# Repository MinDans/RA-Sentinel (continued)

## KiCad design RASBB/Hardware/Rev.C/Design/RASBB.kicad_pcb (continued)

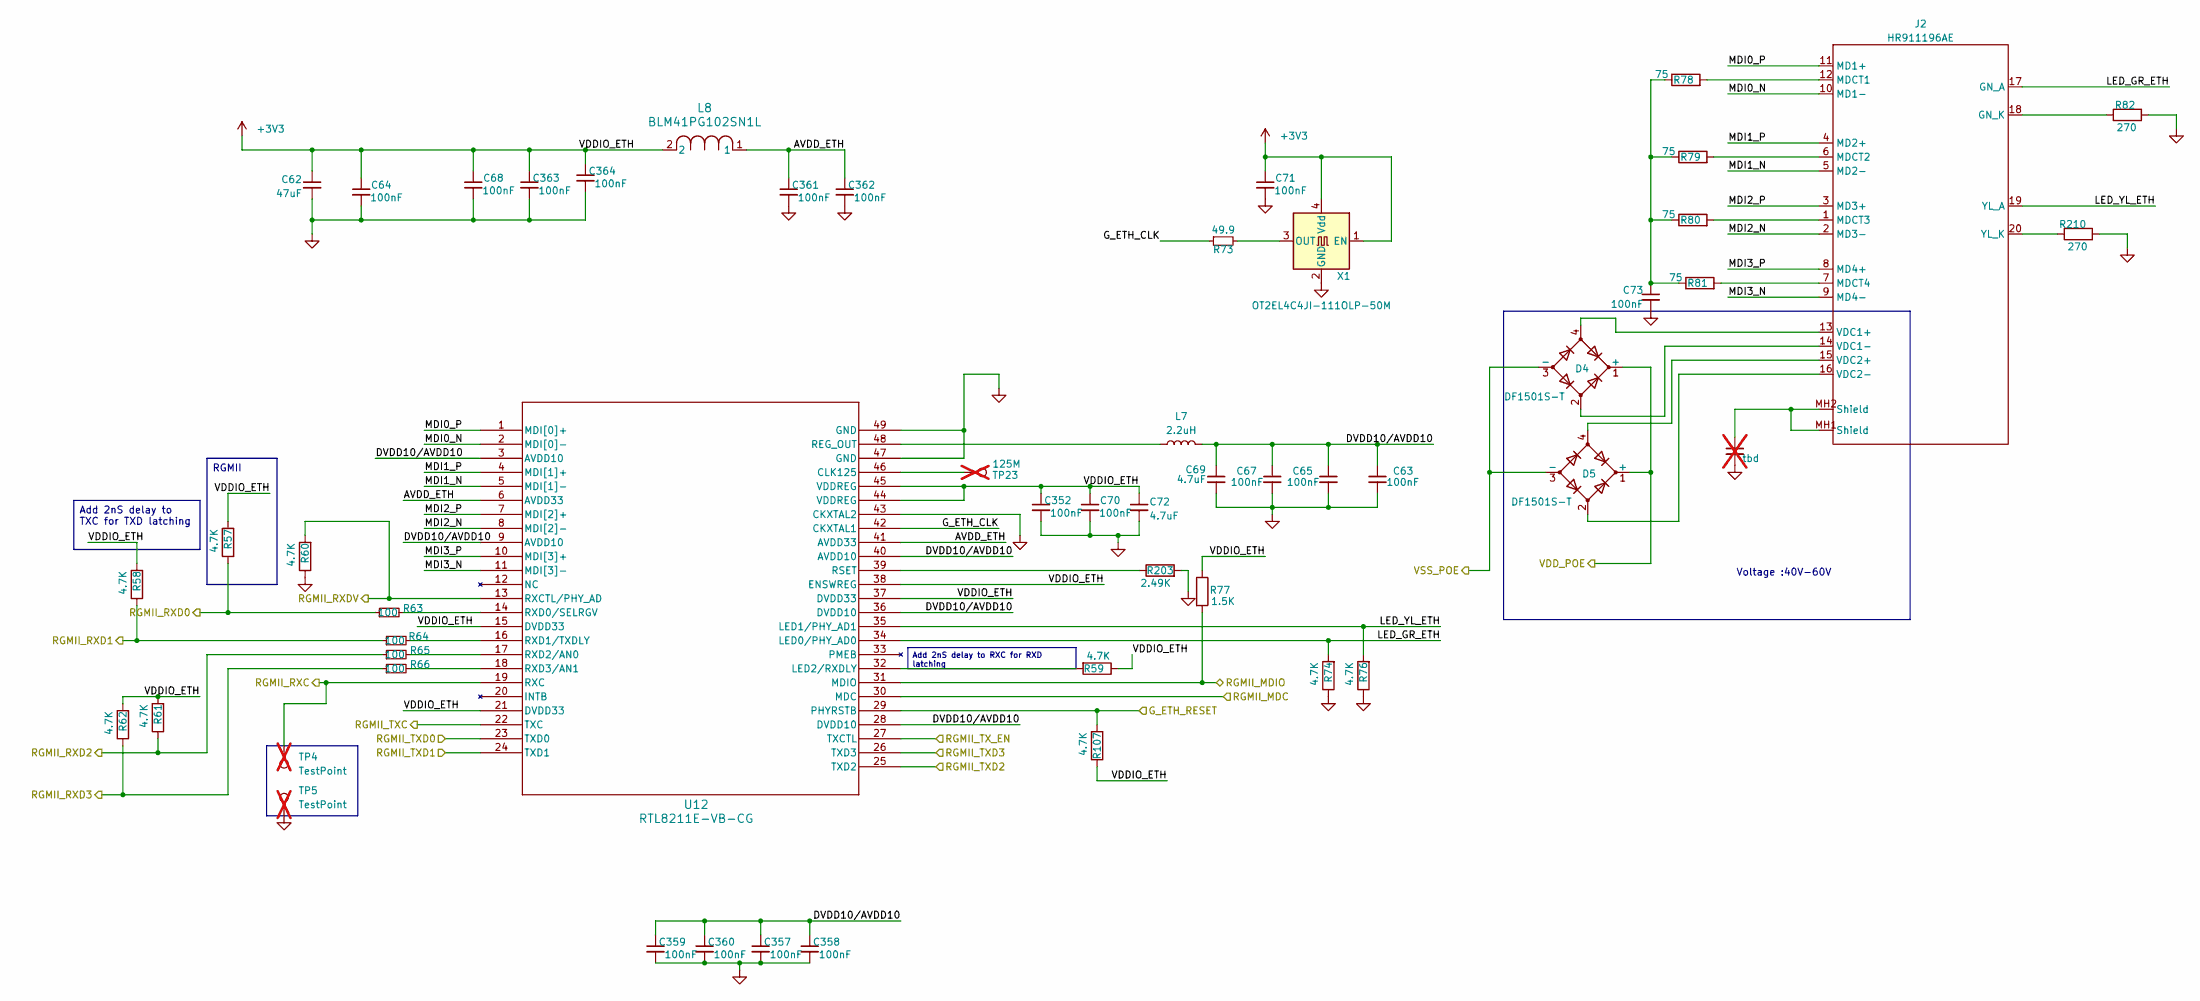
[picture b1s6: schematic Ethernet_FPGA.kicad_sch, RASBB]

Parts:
C62: 47uF; C_0805_2012Metric; Mfr. Part # GRM21BR61A476ME15L; LCSC Part # C124129
C63, C64, C65, C67, C68, C70, C71, C352, C357, C358, C359, C360, C361, C362, C363, C364: 100nF; C_0402_1005Metric; Mfr. Part # 0402B104K500CT; LCSC Part # C152814
C69, C72: 4.7uF; C_0402_1005Metric; Mfr. Part # GRM155R61A475KEAAD; LCSC Part # C77004
C73: 100nF; C_2220_5750Metric; Mfr. Part # FV55X104K202EGG; LCSC Part # C5290327
C74: tbd; C_1206_3216Metric; not fitted
D4, D5: DF1501S-T; DF1501ST; Mfr. Part # DF1501S-T; LCSC Part # C155338
J2: HR911196AE; JK00229NL; Mfr. Part # HR911196AE; LCSC Part # C5149194
L7: 2.2uH; L_1206_3216Metric; Mfr. Part # MGFL3216F2R2MT-LF; LCSC Part # C486337
L8: BLM41PG102SN1L; IND_BLM41_1806_MUR-M; Mfr. Part # BLM41PG102SN1L; LCSC Part # C88999
R57, R58, R59, R60, R61, R62, R74, R76, R107: 4.7K; R_0402_1005Metric; Mfr. Part # WR04X4701FTL; LCSC Part # C163826
R63, R64, R65, R66: 100; R_0402_1005Metric; Mfr. Part # WR04X1000FTL; LCSC Part # C163808
R73: 49.9; R_0402_1005Metric; Mfr. Part # RMCF0402FT49R9; LCSC Part # C4229190
R77: 1.5K; R_0402_1005Metric; Mfr. Part # WR04X152JTL; LCSC Part # C384376
R78, R79, R80, R81: 75; R_0603_1608Metric; Mfr. Part # ESR03EZPF75R0; LCSC Part # C2074227
R82, R210: 270; R_0402_1005Metric; Mfr. Part # SR04X271JTL; LCSC Part # C880838
R203: 2.49K; R_0402_1005Metric; Mfr. Part # RC0402FR-072K49L; LCSC Part # C114768
TP4, TP5: TestPoint; TestPoint_Pad_D1.0mm; not fitted
TP23: 125M; TestPoint_Pad_D1.0mm; not fitted
U12: RTL8211E-VB-CG; QFN48_6X6X0P85_RTK; Mfr. Part # RTL8211E-VB-CG; LCSC Part # C90735
X1: OT2EL4C4JI-111OLP-50M; Oscillator_SMD_Abracon_ASE-4Pin_3.2x2.5mm; Mfr. Part # OT2EL4C4JI-111OLP-50M; LCSC Part # C5203552

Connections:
+3V3: C62.1, C64.1, C68.1, C70.1, C71.1, C72.1, C352.1, C363.1, C364.1, L8.2, R57.2, R58.2, R59.1, R61.2, R62.2, R77.1, R107.1, U12.15 (DVDD33), U12.21 (DVDD33), U12.37 (DVDD33), U12.38 (ENSWREG), U12.44 (VDDREG), U12.45 (VDDREG), X1.1 (EN), X1.4 (Vdd); also elsewhere on the board
/Ethernet_FPGA/AVDD_ETH: C361.1, C362.1, L8.1, U12.6 (AVDD33), U12.41 (AVDD33)
/Ethernet_FPGA/DVDD10/AVDD10: C63.1, C65.1, C67.1, C69.1, C357.1, C358.1, C359.1, C360.1, L7.1, U12.3 (AVDD10), U12.9 (AVDD10), U12.28 (DVDD10), U12.36 (DVDD10), U12.40 (AVDD10)
/Ethernet_FPGA/G_ETH_CLK: R73.1, U12.42 (CKXTAL1)
/Ethernet_FPGA/G_ETH_RESET: R107.2, U12.29 (PHYRSTB); also elsewhere on the board
/Ethernet_FPGA/LED_GR_ETH: J2.17 (GN_A), R74.2, U12.34 (LED0/PHY_AD0)
/Ethernet_FPGA/LED_YL_ETH: J2.19 (YL_A), R76.2, U12.35 (LED1/PHY_AD1)
/Ethernet_FPGA/MDI0_N: J2.10 (MD1-), U12.2 (MDI[0]-)
/Ethernet_FPGA/MDI0_P: J2.11 (MD1+), U12.1 (MDI[0]+)
/Ethernet_FPGA/MDI1_N: J2.5 (MD2-), U12.5 (MDI[1]-)
/Ethernet_FPGA/MDI1_P: J2.4 (MD2+), U12.4 (MDI[1]+)
/Ethernet_FPGA/MDI2_N: J2.2 (MD3-), U12.8 (MDI[2]-)
/Ethernet_FPGA/MDI2_P: J2.3 (MD3+), U12.7 (MDI[2]+)
/Ethernet_FPGA/MDI3_N: J2.9 (MD4-), U12.11 (MDI[3]-)
/Ethernet_FPGA/MDI3_P: J2.8 (MD4+), U12.10 (MDI[3]+)
/Ethernet_FPGA/RGMII_MDC: U12.30 (MDC); also elsewhere on the board
/Ethernet_FPGA/RGMII_MDIO: R77.2, U12.31 (MDIO); also elsewhere on the board
/Ethernet_FPGA/RGMII_RXC: TP4.1 (1_1), U12.19 (RXC); also elsewhere on the board
/Ethernet_FPGA/RGMII_RXD0: R57.1, R63.1; also elsewhere on the board
/Ethernet_FPGA/RGMII_RXD1: R58.1, R64.1; also elsewhere on the board
/Ethernet_FPGA/RGMII_RXD2: R61.1, R65.1; also elsewhere on the board
/Ethernet_FPGA/RGMII_RXD3: R62.1, R66.1; also elsewhere on the board
/Ethernet_FPGA/RGMII_RXDV: R60.2, U12.13 (RXCTL/PHY_AD); also elsewhere on the board
/Ethernet_FPGA/RGMII_TXC: U12.22 (TXC); also elsewhere on the board
/Ethernet_FPGA/RGMII_TXD0: U12.23 (TXD0); also elsewhere on the board
/Ethernet_FPGA/RGMII_TXD1: U12.24 (TXD1); also elsewhere on the board
/Ethernet_FPGA/RGMII_TXD2: U12.25 (TXD2); also elsewhere on the board
/Ethernet_FPGA/RGMII_TXD3: U12.26 (TXD3); also elsewhere on the board
/Ethernet_FPGA/RGMII_TX_EN: U12.27 (TXCTL); also elsewhere on the board
/VDC_IN: D4.1 (+), D5.1 (+); also elsewhere on the board
/VSS_POE: D4.3 (-), D5.3 (-); also elsewhere on the board
GND: C62.2, C63.2, C64.2, C65.2, C67.2, C68.2, C69.2, C70.2, C71.2, C72.2, C73.2, C74.2, C352.2, C357.2, C358.2, C359.2, C360.2, C361.2, C362.2, C363.2, C364.2, R60.1, R74.1, R76.1, R82.2, R203.2, R210.2, TP5.1 (1_1), U12.43 (CKXTAL2), U12.47 (GND), U12.49 (GND), X1.2 (GND); also elsewhere on the board
unnamed: C73.1, R78.1, R79.1, R80.1, R81.1
unnamed: C74.1, J2.MH1 (Shield), J2.MH2 (Shield)
unnamed: J2.18 (GN_K), R82.1
unnamed: J2.12 (MDCT1), R78.2
unnamed: J2.6 (MDCT2), R79.2
unnamed: J2.1 (MDCT3), R80.2
unnamed: J2.7 (MDCT4), R81.2
unnamed: D4.4, J2.13 (VDC1+)
unnamed: D4.2, J2.14 (VDC1-)
unnamed: D5.4, J2.15 (VDC2+)
unnamed: D5.2, J2.16 (VDC2-)
unnamed: J2.20 (YL_K), R210.1
unnamed: TP23.1 (1_1), U12.46 (CLK125)
unnamed: R59.2, U12.32 (LED2/RXDLY)
unnamed: L7.2, U12.48 (REG_OUT)
unnamed: R203.1, U12.39 (RSET)
unnamed: R63.2, U12.14 (RXD0/SELRGV)
unnamed: R64.2, U12.16 (RXD1/TXDLY)
unnamed: R65.2, U12.17 (RXD2/AN0)
unnamed: R66.2, U12.18 (RXD3/AN1)
unnamed: R73.2, X1.3 (OUT)

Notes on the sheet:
Voltage :40V-60V
Add 2nS delay to TXC for TXD latching
RGMII
Add 2nS delay to RXC for RXD latching

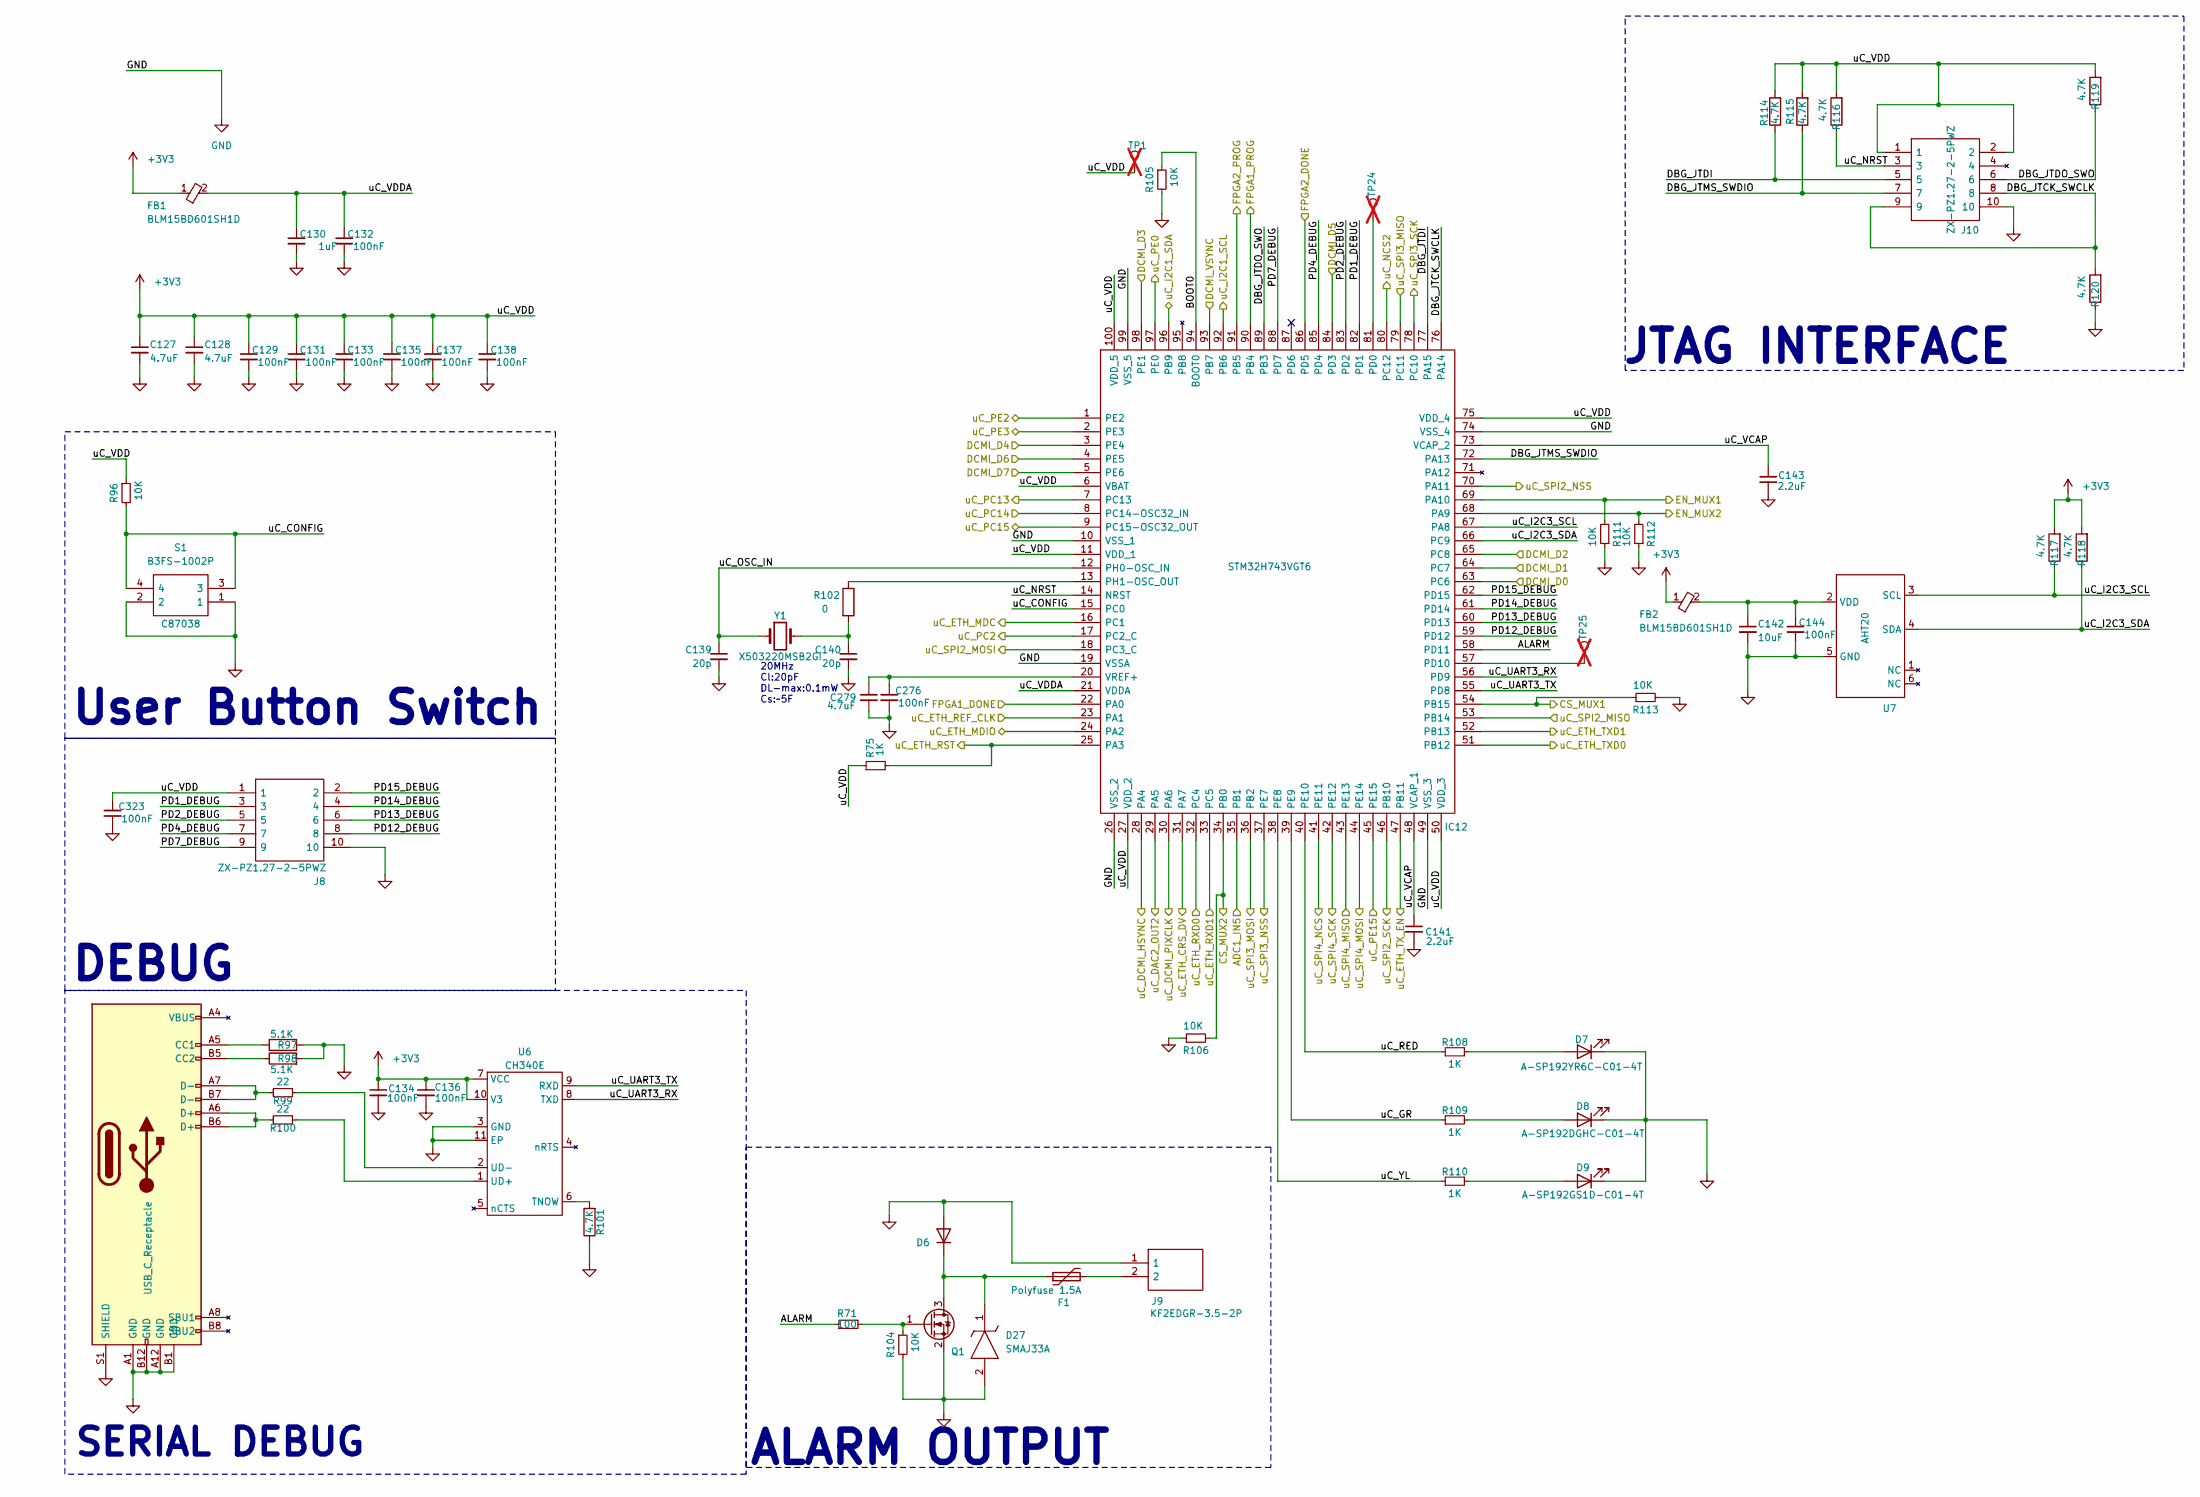
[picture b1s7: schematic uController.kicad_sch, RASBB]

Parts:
C127, C128, C279: 4.7uF; C_0603_1608Metric; Mfr. Part # GMK107BBJ475KA-T; LCSC Part # C7281848
C129, C131, C132, C133, C134, C135, C136, C137, C138, C144, C276, C323: 100nF; C_0402_1005Metric; Mfr. Part # 0402B104K500CT; LCSC Part # C152814
C130: 1uF; C_0402_1005Metric; Mfr. Part # 0402X105M160CT; LCSC Part # C3889771
C139, C140: 20p; C_0402_1005Metric; Mfr. Part # 0402N200J500CT; LCSC Part # C123468
C141, C143: 2.2uF; C_0402_1005Metric; Mfr. Part # 0402X225M160CT; LCSC Part # C3905586
C142: 10uF; C_0402_1005Metric; Mfr. Part # 0402X106M100CT; LCSC Part # C2992625
D6: S210_R1_00001; D_SMB; Mfr. Part # S210_R1_00001; LCSC Part # C391676
D7: A-SP192YR6C-C01-4T; LED_0603_1608Metric; Mfr. Part # A-SP192YR6C-C01-4T; LCSC Part # C5355433
D8: A-SP192DGHC-C01-4T; LED_0603_1608Metric; Mfr. Part # A-SP192DGHC-C01-4T; LCSC Part # C19171301
D9: A-SP192GS1D-C01-4T; LED_0603_1608Metric; Mfr. Part # A-SP192GS1D-C01-4T; LCSC Part # C5355434
D27: SMAJ33A; DIOM5026X229N; Mouser Part Number 576-SMAJ33A
F1: Polyfuse 1.5A; BSMD1812; Mfr. Part # BSMD1812-150-33V; LCSC Part # C883154
FB1, FB2: BLM15BD601SH1D; NFZ15SG152SN10B; Mfr. Part # BLM15BD601SH1D; LCSC Part # C710334
IC12: STM32H743VGT6; QFP50P1600X1600X160-100N; Mfr. Part # STM32H743VGT6; LCSC Part # C730183
J7: USB_C_Receptacle; USB_C_Receptacle_Palconn_UTC16-G; Mfr. Part # TYPE-C 16PIN 2MD(073); LCSC Part # C2765186
J8, J10: ZX-PZ1.27-2-5PWZ; PinHeader_2x05_P1.27mm_Vertical_SMD; Mfr. Part # ZX-PZ1.27-2-5PWZ; LCSC Part # C41370773
J9: KF2EDGR-3.5-2P; SHDRRA2W80P0X350_1X2_1050X920X750P; Mfr. Part # KF2EDGR-3.5-2P; LCSC Part # C441171
Q1: DMN6075S; SOT-23; Mfr. Part # DMN6075S; LCSC Part # C5122015
R71: 100; R_0402_1005Metric; Mfr. Part # WR04X1000FTL; LCSC Part # C163808
R75, R108, R109, R110: 1K; R_0402_1005Metric; Mfr. Part # MR04X1001FTL; LCSC Part # C327796
R96, R104, R105, R106, R111, R112, R113: 10K; R_0402_1005Metric; Mfr. Part # WR04X1002FTL; LCSC Part # C163810
R97, R98: 5.1K; R_0402_1005Metric; Mfr. Part # WR04X512JTL; LCSC Part # C384321
R99, R100: 22; R_0402_1005Metric; Mfr. Part # WR04X22R0FTL; LCSC Part # C163821
R101, R114, R115, R116, R117, R118, R119, R120: 4.7K; R_0402_1005Metric; Mfr. Part # WR04X4701FTL; LCSC Part # C163826
R102: 0; R_0402_1005Metric; Mfr. Part # MR04X000PTL; LCSC Part # C396825
S1: B3FS-1002P; B3FS-1000P; Mfr. Part # B3FS-1002P; LCSC Part # C87038
TP1, TP24, TP25: TestPoint; TestPoint_Pad_D1.0mm; not fitted
U6: CH340E; MSOP-10-1EP_3x3mm_P0.5mm_EP1.68x1.88mm; Mfr. Part # CH340E; LCSC Part # C99652
U7: AHT20; Mfr. Part # AHT20; LCSC Part # C2757850
Y1: X503220MSB2GI; Mfr. Part # X503220MSB2GI; LCSC Part # C112566

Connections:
+3V3: C127.1, C128.1, C129.1, C131.1, C133.1, C134.1, C135.1, C136.1, C137.1, C138.1, C323.1, FB1.1, FB2.1, IC12.6 (VBAT), IC12.11 (VDD_1), IC12.27 (VDD_2), IC12.50 (VDD_3), IC12.75 (VDD_4), IC12.100 (VDD_5), J8.1, J10.1, J10.2, R75.1, R96.1, R114.2, R115.2, R116.2, R117.2, R118.2, R119.2, TP1.1 (1_1), U6.7 (VCC), U6.10 (V3); also elsewhere on the board
/Audio_IN-OUT/Audio_PTT: IC12.45 (PE15); also elsewhere on the board
/CS2_FLASH_uC: IC12.80 (PC12); also elsewhere on the board
/CS_FLASH_uC: IC12.41 (PE11); also elsewhere on the board
/Config-SPI FLASH/MUX_EN1: IC12.69 (PA10), R111.2; also elsewhere on the board
/Config-SPI FLASH/MUX_EN2: IC12.68 (PA9), R112.2; also elsewhere on the board
/Config-SPI FLASH/SWITCH_FLASH_1: IC12.54 (PB15), R113.1; also elsewhere on the board
/Config-SPI FLASH/SWITCH_FLASH_2: IC12.34 (PB0), R106.2; also elsewhere on the board
/Ethernet_uC/ETH_RESET: IC12.25 (PA3), R75.2; also elsewhere on the board
/Ethernet_uC/RMII_MDC: IC12.16 (PC1); also elsewhere on the board
/Ethernet_uC/RMII_MDIO: IC12.24 (PA2); also elsewhere on the board
/Ethernet_uC/RMII_TX_EN: IC12.47 (PB11); also elsewhere on the board
/FPGA1_RESET: IC12.97 (PE0); also elsewhere on the board
/FPGA2_RESET: IC12.17 (PC2_C); also elsewhere on the board
/FPGA-01/BANK0/FPGA1_DONE: IC12.22 (PA0); also elsewhere on the board
/FPGA-01/FPGA1_PROG: IC12.90 (PB4); also elsewhere on the board
/FPGA-02/BANK0/FPGA2_DONE: IC12.86 (PD5); also elsewhere on the board
/FPGA-02/F2_B14_P15: IC12.98 (PE1); also elsewhere on the board
/FPGA-02/F2_B14_R15: IC12.3 (PE4); also elsewhere on the board
/FPGA-02/F2_B14_R16: IC12.4 (PE5); also elsewhere on the board
/FPGA-02/F2_B14_T15: IC12.5 (PE6); also elsewhere on the board
/FPGA-02/F2_B14_T16: IC12.28 (PA4); also elsewhere on the board
/FPGA-02/F2_B14_U14: IC12.64 (PC7); also elsewhere on the board
/FPGA-02/F2_B14_U16: IC12.30 (PA6); also elsewhere on the board
/FPGA-02/F2_B14_V14: IC12.63 (PC6); also elsewhere on the board
/FPGA-02/F2_B14_V15: IC12.65 (PC8); also elsewhere on the board
/FPGA-02/F2_B14_V16: IC12.84 (PD3); also elsewhere on the board
/FPGA-02/F2_B14_V17: IC12.93 (PB7); also elsewhere on the board
/FPGA-02/FPGA2_PROG: IC12.91 (PB5); also elsewhere on the board
/PCIE/PCIE_CS: IC12.37 (PE7); also elsewhere on the board
/PCIE/SMCLK: IC12.92 (PB6); also elsewhere on the board
/PCIE/SMDAT: IC12.96 (PB9); also elsewhere on the board
/RF_Transceiver/BUSY_LORA_G: IC12.8 (PC14-OSC32_IN); also elsewhere on the board
/RF_Transceiver/DIO1_LORA_G: IC12.1 (PE2); also elsewhere on the board
/RF_Transceiver/DIO2_LORA_G: IC12.2 (PE3); also elsewhere on the board
/RF_Transceiver/DIO3_LORA_G: IC12.9 (PC15-OSC32_OUT); also elsewhere on the board
/RF_Transceiver/NRST_LORA_G: IC12.7 (PC13); also elsewhere on the board
/RF_Transceiver/SPI_NSS_LORA_G: IC12.70 (PA11); also elsewhere on the board
/SO_FLASH_uC: IC12.43 (PE13); also elsewhere on the board
/uController/ADC1_IN5: IC12.35 (PB1); also elsewhere on the board
/uController/ALARM: IC12.58 (PD11), R71.1
/uController/BOOT0: IC12.94 (BOOT0), R105.1
/uController/DBG_JTCK_SWCLK: IC12.76 (PA14), J10.8, J10.9, R120.2
/uController/DBG_JTDI: IC12.77 (PA15), J10.5, R114.1
/uController/DBG_JTDO_SWO: IC12.89 (PB3), J10.6, R119.1
/uController/DBG_JTMS_SWDIO: IC12.72 (PA13), J10.7, R115.1
/uController/PD1_DEBUG: IC12.82 (PD1), J8.3
/uController/PD2_DEBUG: IC12.83 (PD2), J8.5
/uController/PD4_DEBUG: IC12.85 (PD4), J8.7
/uController/PD7_DEBUG: IC12.88 (PD7), J8.9
/uController/PD12_DEBUG: IC12.59 (PD12), J8.8
/uController/PD13_DEBUG: IC12.60 (PD13), J8.6
/uController/PD14_DEBUG: IC12.61 (PD14), J8.4
/uController/PD15_DEBUG: IC12.62 (PD15), J8.2
/uController/uC_CONFIG: IC12.15 (PC0), R96.2, S1.3, S1.4
/uController/uC_DAC2_OUT2: IC12.29 (PA5); also elsewhere on the board
/uController/uC_ETH_CRS_DV: IC12.31 (PA7); also elsewhere on the board
/uController/uC_ETH_REF_CLK: IC12.23 (PA1); also elsewhere on the board
/uController/uC_ETH_RXD0: IC12.32 (PC4); also elsewhere on the board
/uController/uC_ETH_RXD1: IC12.33 (PC5); also elsewhere on the board
/uController/uC_ETH_TXD0: IC12.51 (PB12); also elsewhere on the board
/uController/uC_ETH_TXD1: IC12.52 (PB13); also elsewhere on the board
/uController/uC_GR: IC12.39 (PE9), R109.1
/uController/uC_I2C3_SCL: IC12.67 (PA8), R117.1, U7.3 (SCL)
/uController/uC_I2C3_SDA: IC12.66 (PC9), R118.1, U7.4 (SDA)
/uController/uC_NRST: IC12.14 (NRST), J10.3, R116.1
/uController/uC_OSC_IN: C139.1, IC12.12 (PH0-OSC_IN), Y1.1
/uController/uC_RED: IC12.40 (PE10), R108.1
/uController/uC_SPI2_MISO: IC12.53 (PB14); also elsewhere on the board
/uController/uC_SPI2_MOSI: IC12.18 (PC3_C); also elsewhere on the board
/uController/uC_SPI2_SCK: IC12.46 (PB10); also elsewhere on the board
/uController/uC_SPI3_MISO: IC12.79 (PC11); also elsewhere on the board
/uController/uC_SPI3_MOSI: IC12.36 (PB2); also elsewhere on the board
/uController/uC_SPI3_SCK: IC12.78 (PC10); also elsewhere on the board
/uController/uC_SPI4_MOSI: IC12.44 (PE14); also elsewhere on the board
/uController/uC_SPI4_SCK: IC12.42 (PE12); also elsewhere on the board
/uController/uC_UART3_RX: IC12.56 (PD9), U6.8 (TXD)
/uController/uC_UART3_TX: IC12.55 (PD8), U6.9 (RXD)
/uController/uC_VCAP: C141.1, C143.1, IC12.48 (VCAP_1), IC12.73 (VCAP_2)
/uController/uC_VDDA: C130.1, C132.1, FB1.2, IC12.21 (VDDA)
/uController/uC_YL: IC12.38 (PE8), R110.1
GND: C127.2, C128.2, C129.2, C130.2, C131.2, C132.2, C133.2, C134.2, C135.2, C136.2, C137.2, C138.2, C139.2, C140.2, C141.2, C142.2, C143.2, C144.2, C276.2, C279.2, C323.2, D6.2 (A), D7.1 (K), D8.1 (K), D9.1 (K), D27.2, IC12.10 (VSS_1), IC12.19 (VSSA), IC12.26 (VSS_2), IC12.49 (VSS_3), IC12.74 (VSS_4), IC12.99 (VSS_5), J7.A1 (GND), J7.A12 (GND), J7.B1 (GND), J7.B12 (GND), J7.S1 (SHIELD), J8.10, J9.1, J10.10, Q1.2 (S), R97.2, R98.2, R101.1, R104.2, R105.2, R106.1, R111.1, R112.1, R113.2, R120.1, S1.1, S1.2, U6.3 (GND), U6.11 (EP), U7.5 (GND); also elsewhere on the board
unnamed: C140.1, R102.2, Y1.2
unnamed: D6.1 (K), D27.1, F1.1, Q1.3 (D)
unnamed: D7.2 (A), R108.2
unnamed: D8.2 (A), R109.2
unnamed: D9.2 (A), R110.2
unnamed: F1.2, J9.2
unnamed: IC12.81 (PD0), TP24.1 (1_1)
unnamed: IC12.57 (PD10), TP25.1 (1_1)
unnamed: IC12.13 (PH1-OSC_OUT), R102.1
unnamed: C276.1, C279.1, IC12.20 (VREF+)
unnamed: J7.A5 (CC1), R97.1
unnamed: J7.B5 (CC2), R98.1
unnamed: J7.A6 (D+), J7.B6 (D+), R100.2
unnamed: J7.A7 (D-), J7.B7 (D-), R99.2
unnamed: Q1.1 (G), R71.2, R104.1
unnamed: R101.2, U6.6 (TNOW)
unnamed: R100.1, U6.1 (UD+)
unnamed: R99.1, U6.2 (UD-)
unnamed: C142.1, C144.1, FB2.2, U7.2 (VDD)

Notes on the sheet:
20MHz Cl:20pF DL-max:0.1mW Cs:~5F
DEBUG
SERIAL DEBUG
User Button Switch
ALARM OUTPUT
JTAG INTERFACE

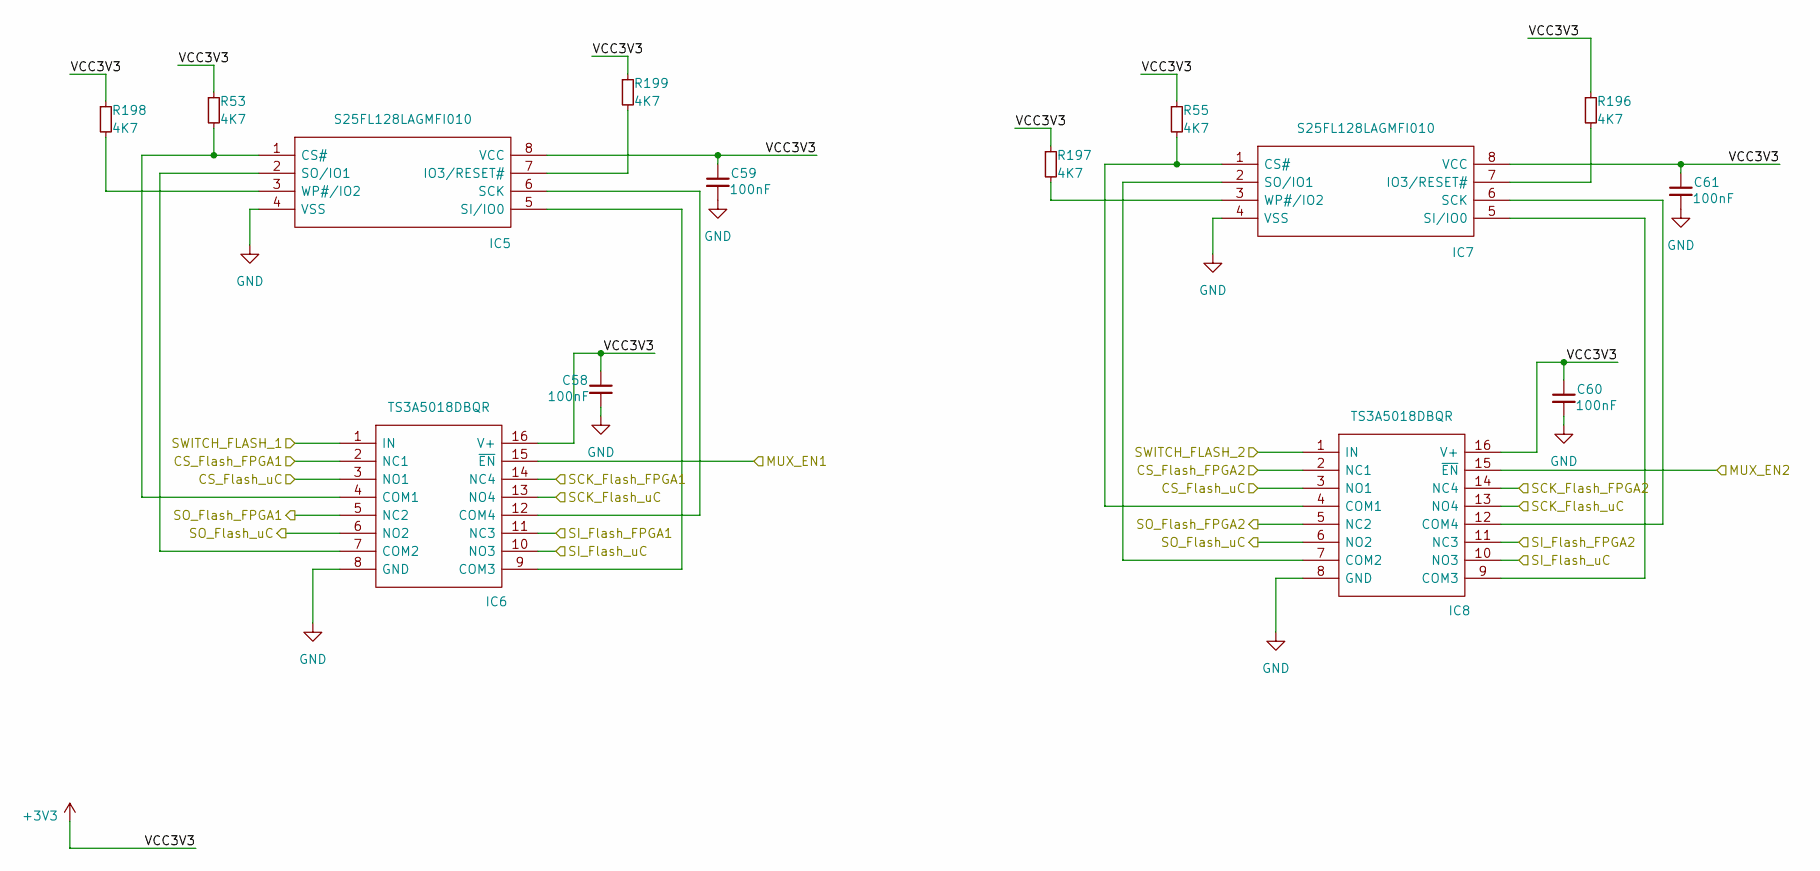
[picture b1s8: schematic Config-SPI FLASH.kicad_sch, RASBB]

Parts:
C58, C59, C60, C61: 100nF; C_0402_1005Metric; Mfr. Part # 0402B104K500CT; LCSC Part # C152814
IC5, IC7: S25FL128LAGMFI010; SOIC127P800X216-8N; Mfr. Part # S25FL128LAGMFI010; LCSC Part # C2959152
IC6, IC8: TS3A5018DBQR; SOP64P600X175-16N; Mfr. Part # TS3A5018DBQR; LCSC Part # C202285
R53, R55, R196, R197, R198, R199: 4K7; R_0402_1005Metric; Mfr. Part # RC0402FR-074K7L; LCSC Part # C105871

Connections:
+3V3: C58.1, C59.1, C60.1, C61.1, IC5.8 (VCC), IC6.16 (V+), IC7.8 (VCC), IC8.16 (V+), R53.1, R55.1, R196.1, R197.1, R198.1, R199.1; also elsewhere on the board
/CS_FLASH_FPGA2: IC8.2 (NC1); also elsewhere on the board
/CS_FLASH_uC: IC6.3 (NO1), IC8.3 (NO1); also elsewhere on the board
/Config-SPI FLASH/CS_Flash_FPGA1: IC6.2 (NC1); also elsewhere on the board
/Config-SPI FLASH/MUX_EN1: IC6.15 (~EN); also elsewhere on the board
/Config-SPI FLASH/MUX_EN2: IC8.15 (~EN); also elsewhere on the board
/Config-SPI FLASH/SCK_Flash_FPGA1: IC6.14 (NC4); also elsewhere on the board
/Config-SPI FLASH/SCK_Flash_FPGA2: IC8.14 (NC4); also elsewhere on the board
/Config-SPI FLASH/SI_Flash_FPGA1: IC6.11 (NC3); also elsewhere on the board
/Config-SPI FLASH/SI_Flash_FPGA2: IC8.11 (NC3); also elsewhere on the board
/Config-SPI FLASH/SO_Flash_FPGA1: IC6.5 (NC2); also elsewhere on the board
/Config-SPI FLASH/SO_Flash_FPGA2: IC8.5 (NC2); also elsewhere on the board
/Config-SPI FLASH/SWITCH_FLASH_1: IC6.1 (IN); also elsewhere on the board
/Config-SPI FLASH/SWITCH_FLASH_2: IC8.1 (IN); also elsewhere on the board
/SCK_FLASH_uC: IC6.13 (NO4), IC8.13 (NO4); also elsewhere on the board
/SI_FLASH_uC: IC6.10 (NO3), IC8.10 (NO3); also elsewhere on the board
/SO_FLASH_uC: IC6.6 (NO2), IC8.6 (NO2); also elsewhere on the board
GND: C58.2, C59.2, C60.2, C61.2, IC5.4 (VSS), IC6.8 (GND), IC7.4 (VSS), IC8.8 (GND); also elsewhere on the board
unnamed: IC5.1 (CS#), IC6.4 (COM1), R53.2
unnamed: IC5.7 (IO3/RESET#), R199.2
unnamed: IC5.6 (SCK), IC6.12 (COM4)
unnamed: IC5.5 (SI/IO0), IC6.9 (COM3)
unnamed: IC5.2 (SO/IO1), IC6.7 (COM2)
unnamed: IC5.3 (WP#/IO2), R198.2
unnamed: IC7.1 (CS#), IC8.4 (COM1), R55.2
unnamed: IC7.7 (IO3/RESET#), R196.2
unnamed: IC7.6 (SCK), IC8.12 (COM4)
unnamed: IC7.5 (SI/IO0), IC8.9 (COM3)
unnamed: IC7.2 (SO/IO1), IC8.7 (COM2)
unnamed: IC7.3 (WP#/IO2), R197.2

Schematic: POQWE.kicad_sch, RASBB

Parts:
C3, C7: 10nF; C_0603_1608Metric; Mfr. Part # CGA0603X7R103K101JT; LCSC Part # C6119837
C4: 10uF/100V; C_1206_3216Metric; Mfr. Part # C3216X6S2A106K160AC; LCSC Part # C6872041
C5, C6: 4.7uF; C_1206_3216Metric; Mfr. Part # GRM31CZ72A475KE11L; LCSC Part # C2997285
C8: 22pF; C_0402_1005Metric; Mfr. Part # CC0402JRNPO7BN220; LCSC Part # C2175872
C9: 4.7nF; C_0402_1005Metric; Mfr. Part # CC0402KRX7R6BB472; LCSC Part # C1852867
C10, C16, C18, C27, C28, C31, C33, C34, C35, C36, C37, C55, C356: 100nF; C_0402_1005Metric; Mfr. Part # 0402B104K500CT; LCSC Part # C152814
C11, C38, C39, C40, C50, C51: 10nF; C_0402_1005Metric; Mfr. Part # 0402B103K500CT; LCSC Part # C301927
C12, C13, C14, C15, C21, C22, C23, C24, C25, C26: 10uF; C_1206_3216Metric; Mfr. Part # CGA5L1X7R1H106KT0Y0N; LCSC Part # C531431
C17: 33uF; EEE0JA152UAP; Mfr. Part # EEE-FP1V330AP; LCSC Part # C178581
C19: 1uF; C_0402_1005Metric; Mfr. Part # 0402X105M160CT; LCSC Part # C3889771
C20: 4.7uF; C_0402_1005Metric; Mfr. Part # GRM155R61A475KEAAD; LCSC Part # C77004
C29: 4.7uF; C_0603_1608Metric; Mfr. Part # GMK107BBJ475KA-T; LCSC Part # C7281848
C30, C32: 470nF; C_0402_1005Metric; Mfr. Part # GRT155R71A474KE01D; LCSC Part # C471404
C41: 10pF; C_0402_1005Metric; Mfr. Part # C0402C100J4GAC7867; LCSC Part # C2182752
C42, C46, C49, C52: 47uF; C_0805_2012Metric; Mfr. Part # GRM21BR61A476ME15L; LCSC Part # C124129
C43: 5.1pF; C_0402_1005Metric; Mfr. Part # GRM1555C1E5R1CA01D; LCSC Part # C3855079
C44, C45, C47, C48, C53, C54, C56, C57: 22uF; C_0603_1608Metric; Mfr. Part # 0603YD226MAT2A; LCSC Part # C6776252
C354, C355: 2.2uF; C_0805_2012Metric; Mfr. Part # 0805B225K500CT; LCSC Part # C2918681
D1: SDT5A60SA-13; SDT5A60SA13; Mfr. Part # SDT5A60SA-13; LCSC Part # C3024223
D2, D3: VSSAF5L45HM3_A_H; SODFL5226X100N; Mfr. Part # VSSAF5L45HM3_A/H; LCSC Part # C6000165
D17, D18, D19, D20, D21: A-SP192DGHC-C01-4T; LED_0603_1608Metric; Mfr. Part # A-SP192DGHC-C01-4T; LCSC Part # C19171301
F2: Polyfuse 2A; BSMD1812; Mfr. Part # BSMD1812-200-30V; LCSC Part # C960026
IC1: RT6365GSP; SOIC127P600X175-9N; Mfr. Part # RT6365GSP; LCSC Part # C3024482
IC2, IC4: TPS56528DDAR; SOIC127P600X170-9N; Mfr. Part # TPS56528DDAR; LCSC Part # C138716
IC3: TPS563201DDCR; SOT95P280X110-6N; Mfr. Part # TPS563201DDCR; LCSC Part # C116592
J1: PJ-002AH-SMT-TR; CUI_PJ-002AH-SMT-TR; Mfr. Part # PJ-002AH-SMT-TR; LCSC Part # C22434687
L1: 10uH; 0630CDMCDDS-100MC; Mfr. Part # 0630CDMCDDS-100MC; LCSC Part # C2595948
L2: 15uH; SMDRS6028-150N; Mfr. Part # SMDRS6028-150N; LCSC Part # C163563
L3: 360nH; INDPM109103X400N; Mfr. Part # IHLP4040DZERR36M01; LCSC Part # C845083
L4, L5, L6: 2.2uH; IND_IHLP-2525CZ_VIS; Mfr. Part # IHLP2525EZER2R2M01; LCSC Part # C845037
R25: 24.9K; R_1206_3216Metric; Mfr. Part # WR12X2492FTL; LCSC Part # C171074
R26: 249K; R_0805_2012Metric; Mfr. Part # WR08X2493FTL; LCSC Part # C170853
R27: 51K; R_0603_1608Metric; Mfr. Part # WR06X5102FTL; LCSC Part # C227390
R28: 590K; R_0402_1005Metric; Mfr. Part # WR04X5903FTL; LCSC Part # C172103
R29, R30: 18K; R_0402_1005Metric; Mfr. Part # WR04X1802FTL; LCSC Part # C168206
R31: 120K; R_0402_1005Metric; Mfr. Part # RC0402JR-07120KL; LCSC Part # C137924
R32, R44: 3.3; R_0402_1005Metric; Mfr. Part # CRCW04023R30FKEDC; LCSC Part # C384380
R33: 180K; R_0402_1005Metric; Mfr. Part # WR04X1803FTL; LCSC Part # C168207
R34: 12K; R_0402_1005Metric; Mfr. Part # SR04X1202FTL; LCSC Part # C2991361
R35, R41, R42, R43, R49: 100K; R_0402_1005Metric; Mfr. Part # RC0402FR-07100KL; LCSC Part # C60491; not fitted
R36: 220K; R_0402_1005Metric; Mfr. Part # 0402WGF2203TCE; LCSC Part # C25767
R37: 100K; R_0402_1005Metric; Mfr. Part # RC0402FR-07100KL; LCSC Part # C60491
R38: 5.49K; R_0402_1005Metric; Mfr. Part # CRCW04025K49FKED; LCSC Part # C2092200
R39: 2.32K; R_0402_1005Metric; Mfr. Part # CRCW04022K32FKED; LCSC Part # C2091739
R40: 3.48K; R_0402_1005Metric; Mfr. Part # CRCW04023K48FKED; LCSC Part # C4336043
R45: 11K; R_0402_1005Metric; Mfr. Part # WR04X113JTL; LCSC Part # C172152
R46: 2.1K; R_0402_1005Metric; Mfr. Part # WR04X2101FTL; LCSC Part # C170256
R47: 7.68k; R_0402_1005Metric; Mfr. Part # WR04X7681FTL; LCSC Part # C334733
R48: 10K; R_0402_1005Metric; Mfr. Part # WR04X1002FTL; LCSC Part # C163810
R50, R52: 49.9K; R_0402_1005Metric; Mfr. Part # CRCW040249K9FKED; LCSC Part # C350874
R51: 226K; R_0402_1005Metric; Mfr. Part # CRCW0402226KFKED; LCSC Part # C2076623
R128, R129, R130: 715; R_0402_1005Metric; Mfr. Part # WR04X7150FTL; LCSC Part # C334727
R131, R138: 1K; R_0402_1005Metric; Mfr. Part # MR04X1001FTL; LCSC Part # C327796
R165: 0.005; R_2512_6332Metric; Mfr. Part # FRM252WJR005TN; LCSC Part # C7419996
U1: SZMMSZ4702T1G; SOD-123_ONS; Mfr. Part # SZMMSZ4702T1G; LCSC Part # C463904
U2: SI2324DS-T1-GE3; SOT_4DS-T1-GE3_VIS; Mfr. Part # SI2324DS-T1-GE3; LCSC Part # C190351
U3: SIC453ED-T1-GE3; POWERPAK_MLP34-57_VIS; Mfr. Part # SIC453ED-T1-GE3; LCSC Part # C5334327
U4: JW5026; SOT-23-6; Mfr. Part # JW5026; LCSC Part # C185109
Z1: MMSZ5255BT1G; SOD3716X135N; Mfr. Part # MMSZ5255BT1G; LCSC Part # C242284

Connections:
+1V0: R130.1, R165.1; also elsewhere on the board
+1V8: C41.1, C50.1, C54.2, C57.2, L5.1, R49.1, R128.1; also elsewhere on the board
+1V35: C39.1, C44.2, C47.2, L4.1, R47.1, R129.1; also elsewhere on the board
+3V3: C43.1, C51.1, C53.2, C56.2, L6.1, R51.2, R131.1; also elsewhere on the board
+5V: C40.1, C45.2, C48.2, L2.2, R45.2, R138.1; also elsewhere on the board
/POWER/12.8V: C11.1, C12.1, C13.1, C14.1, C15.1, D2.2, L1.2, R33.1
/POWER/PGOOD_1V: IC2.1 (EN), IC4.1 (EN), R35.2, U3.13 (PGOOD)
/POWER/PGOOD_1V8: C30.1, IC2.3 (VREG5), R41.1
/POWER/PGOOD_3V3: C32.1, IC3.5 (EN), IC4.3 (VREG5), R43.1
/POWER/VSEN_P: C38.1, C42.1, C46.1, C49.1, C52.1, C55.2, L3.2, R165.2, U3.12 (VSEN+)
/VDC_IN: C3.1, C4.1, C5.1, C6.1, C7.1, IC1.2 (VIN), R25.2, R28.1, Z1.1; also elsewhere on the board
/VSS_POE: C3.2, R25.1, R26.1, U1.2, U2.3 (D); also elsewhere on the board
GND: C4.2, C5.2, C6.2, C7.2, C8.2, C9.2, C11.2, C12.2, C13.2, C14.2, C15.2, C16.2, C17.2, C18.2, C19.2, C20.2, C21.2, C22.2, C23.2, C24.2, C25.2, C26.2, C27.2, C28.2, C29.2, C30.2, C31.2, C32.2, C38.2, C39.2, C40.2, C42.2, C44.1, C45.1, C46.2, C47.1, C48.1, C49.2, C50.2, C51.2, C52.2, C53.1, C54.1, C55.1, C56.1, C57.1, C354.2, C355.2, C356.2, D1.2, D17.1 (K), D18.1 (K), D19.1 (K), D20.1 (K), D21.1 (K), IC1.7 (GND_1), IC1.9 (GND_2), IC2.5 (GND), IC2.9 (EP), IC3.1 (GND), IC4.5 (GND), IC4.9 (EP), J1.2, J1.3, R29.1, R31.1, R34.2, R37.1, R38.1, R39.1, R40.1, R46.1, R48.2, R50.1, R52.1, U2.2 (S), U3.7 (AGND), U3.11 (VSEN-), U3.16 (AGND), U3.32/33 (PGND), U4.2 (GND); also elsewhere on the board
unnamed: C9.1, R30.1
unnamed: C10.2, R32.2
unnamed: C16.1, D2.1, D3.1, F2.2
unnamed: C37.2, R44.2
unnamed: D3.2, J1.1A, J1.1B
unnamed: D17.2 (A), R130.2
unnamed: D18.2 (A), R129.2
unnamed: D19.2 (A), R128.2
unnamed: D20.2 (A), R131.2
unnamed: D21.2 (A), R138.2
unnamed: C10.1, IC1.1 (BOOT)
unnamed: C8.1, IC1.6 (COMP), R30.2
unnamed: IC1.3 (EN), R28.2, R29.2
unnamed: IC1.5 (FB), R33.2, R34.1
unnamed: IC1.4 (RT/SYNC), R31.2
unnamed: D1.1, IC1.8 (SW), L1.1, R32.1
unnamed: IC2.4 (PG), R41.2
unnamed: C35.1, IC2.6 (SW), L5.2
unnamed: C35.2, IC2.7 (VBST)
unnamed: C41.2, IC2.2 (VFB), R49.2, R50.2
unnamed: C34.1, IC3.2 (SW), L4.2
unnamed: C34.2, IC3.6 (VBST)
unnamed: IC3.4 (VFB), R47.2, R48.1
unnamed: IC4.4 (PG), R43.2
unnamed: C36.1, IC4.6 (SW), L6.2
unnamed: C36.2, IC4.7 (VBST)
unnamed: C43.2, IC4.2 (VFB), R51.1, R52.2
unnamed: R27.2, Z1.2
unnamed: R26.2, R27.1, U1.1, U2.1 (G)
unnamed: R40.2, U3.14 (ADDR)
unnamed: C37.1, U3.6 (BOOT)
unnamed: R36.1, R37.2, U3.21 (EN)
unnamed: R44.1, U3.4 (PH)
unnamed: R38.2, U3.17 (RT/SYNC)
unnamed: L3.1, U3.26-31 (SW)
unnamed: R39.2, U3.15 (VSET)
unnamed: C20.1, U3.24 (PVCC)
unnamed: C19.1, R35.1, U3.22 (VDD)
unnamed: C33.1, U4.1 (BST)
unnamed: R42.2, U4.4 (EN)
unnamed: R45.1, R46.2, U4.3 (FB)
unnamed: C33.2, L2.1, U4.6 (SW)

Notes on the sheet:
Fsw:800kHz
L->H:39.83 H->L:37.82
VIN(MAX):14V VIN(NOM):12V
VOUT:1.8V(+-4%) IOUT:5A VOUT,ripple:5mV Eff@25degC:82%
VOUT:12.8V IOUT:4A VOUT,ripple:3mV
VOUT:3.32V(+-4%) IOUT:5A VOUT,ripple:8mV Eff@25degC:87%
VOUT:5V IOUT:800mA VOUT,ripple:
VOUT:1VDC
Vin:40-60V
VOUT:1.35V(+-3.5%) IOUT:3A VOUT,ripple:5.5mV Eff@25degC:77%
fsw:800kHz
VEN_Max:4V4
VOUT:1V IOUT:15A VOUT,ripple:3mV Eff@25degC:75-86%
